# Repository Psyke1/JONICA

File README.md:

# JONICA

# ASIGNACION DE TAREAS

· JONI
- Diseño de actuadores para escape de tapas
- Control de motores paso a paso

· PAULA
- //Control de servo
- Comunicacion UART Arduino

· MARIANO
- Comunicacion UART en Python + definición de tramas
- Ver imagen por navegador (opcional)
- Puente H

· OPAMP
- Diseño de maqueta
- Algoritmo de reconocimiento
- Diseño de tolva

· TAREAS PENDIENTES
- Alimentacion a usar
- Motor de tolva (lo dejamos directo?)
- LEDs blancos (los dejamos directos?)
- Definir tramas de comunicación UART
- Probar la tolva

- Colores de tapas:
- Rojo, verde, celeste, amarillo, naranja, gris.

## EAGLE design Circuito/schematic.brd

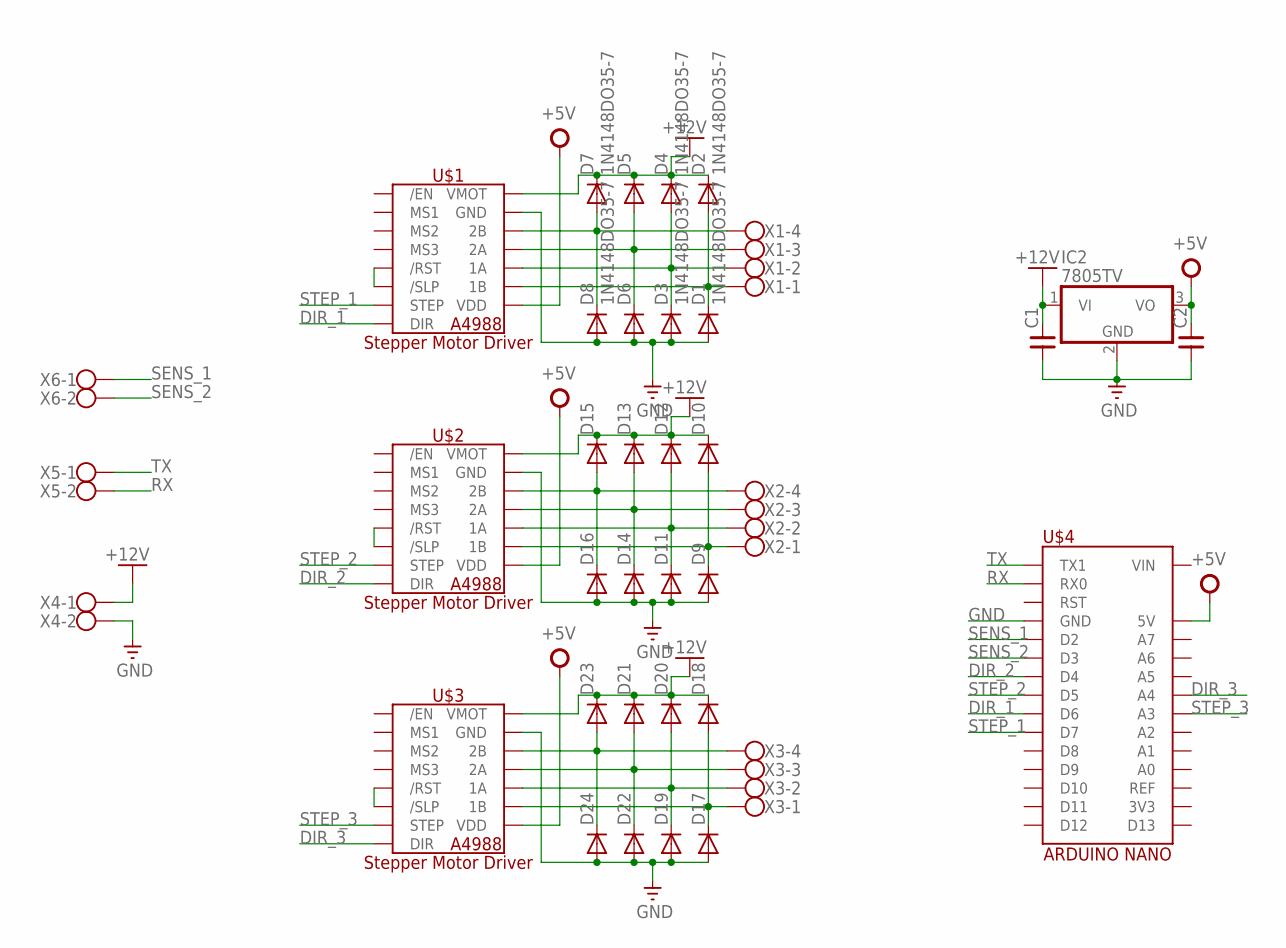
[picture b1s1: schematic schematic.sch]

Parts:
C1, C2: CNP-C035-055X025; C035-055X025
D1, D2, D3, D4, D5, D6, D7, D8, D9, D10, D11, D12, D13, D14, D15, D16, D17, D18, D19, D20, D21, D22, D23, D24: 1N4148DO35-7; DO35-7
IC2: 7805TV; TO220V
U$1, U$2, U$3: A4988_STEP
U$4: NANO_HEADER
X1, X2, X3: W237-4
X4, X5, X6: W237-102

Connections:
+5V: C2.2, IC2.3 (VO), U$1.VDD, U$2.VDD, U$3.VDD, U$4.5V
+12V: C1.2, D2.C, D4.C, D5.C, D7.C, D10.C, D12.C, D13.C, D15.C, D18.C, D20.C, D21.C, D23.C, IC2.1 (VI), U$1.VMOT, U$2.VMOT, U$3.VMOT, X4.1
DIR_1: U$1.DIR, U$4.D6
DIR_2: U$2.DIR, U$4.D4
DIR_3: U$3.DIR, U$4.A4
GND: C1.1, C2.1, D1.A, D3.A, D6.A, D8.A, D9.A, D11.A, D14.A, D16.A, D17.A, D19.A, D22.A, D24.A, IC2.2 (GND), U$1.GND, U$1.GND2 (GND), U$2.GND, U$2.GND2 (GND), U$3.GND, U$3.GND2 (GND), U$4.GND, U$4.GND2 (GND), X4.2
unnamed: D1.C, D2.A, U$1.1B, X1.1
unnamed: U$1./RST, U$1./SLP
unnamed: D9.C, D10.A, U$2.1B, X2.1
unnamed: D3.C, D4.A, U$1.1A, X1.2
unnamed: D11.C, D12.A, U$2.1A, X2.2
unnamed: D5.A, D6.C, U$1.2A, X1.3
unnamed: D7.A, D8.C, U$1.2B, X1.4
unnamed: D13.A, D14.C, U$2.2A, X2.3
unnamed: D15.A, D16.C, U$2.2B, X2.4
unnamed: U$2./RST, U$2./SLP
unnamed: D17.C, D18.A, U$3.1B, X3.1
unnamed: D19.C, D20.A, U$3.1A, X3.2
unnamed: D21.A, D22.C, U$3.2A, X3.3
unnamed: D23.A, D24.C, U$3.2B, X3.4
unnamed: U$3./RST, U$3./SLP
RX: U$4.RX0, X5.2
SENS_1: U$4.D2, X6.1
SENS_2: U$4.D3, X6.2
STEP_1: U$1.STEP, U$4.D7
STEP_2: U$2.STEP, U$4.D5
STEP_3: U$3.STEP, U$4.A3
TX: U$4.TX1, X5.1

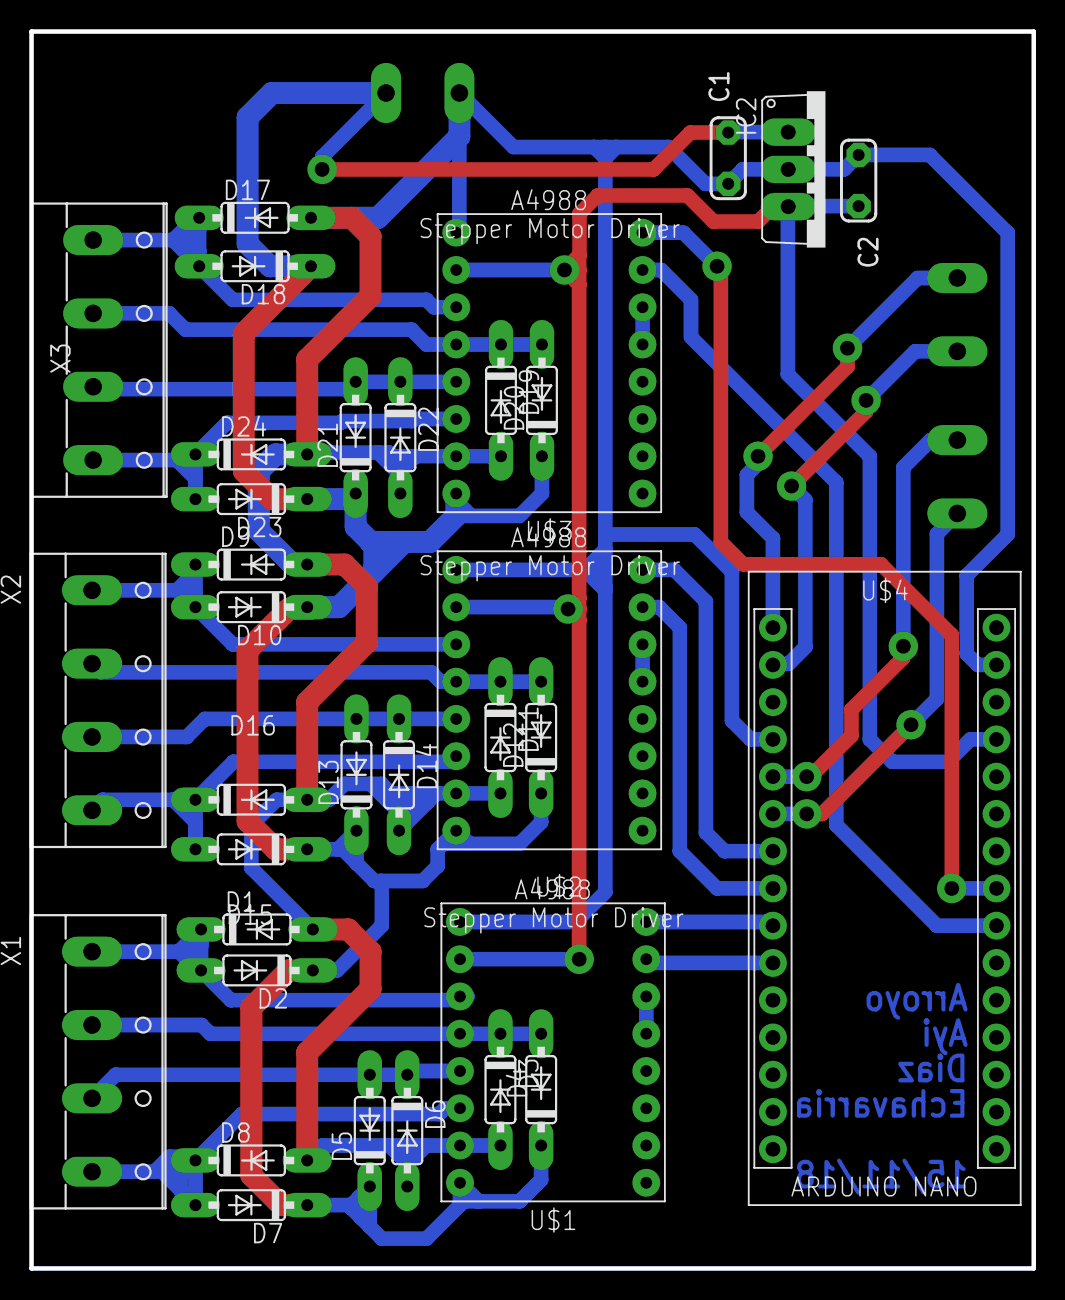
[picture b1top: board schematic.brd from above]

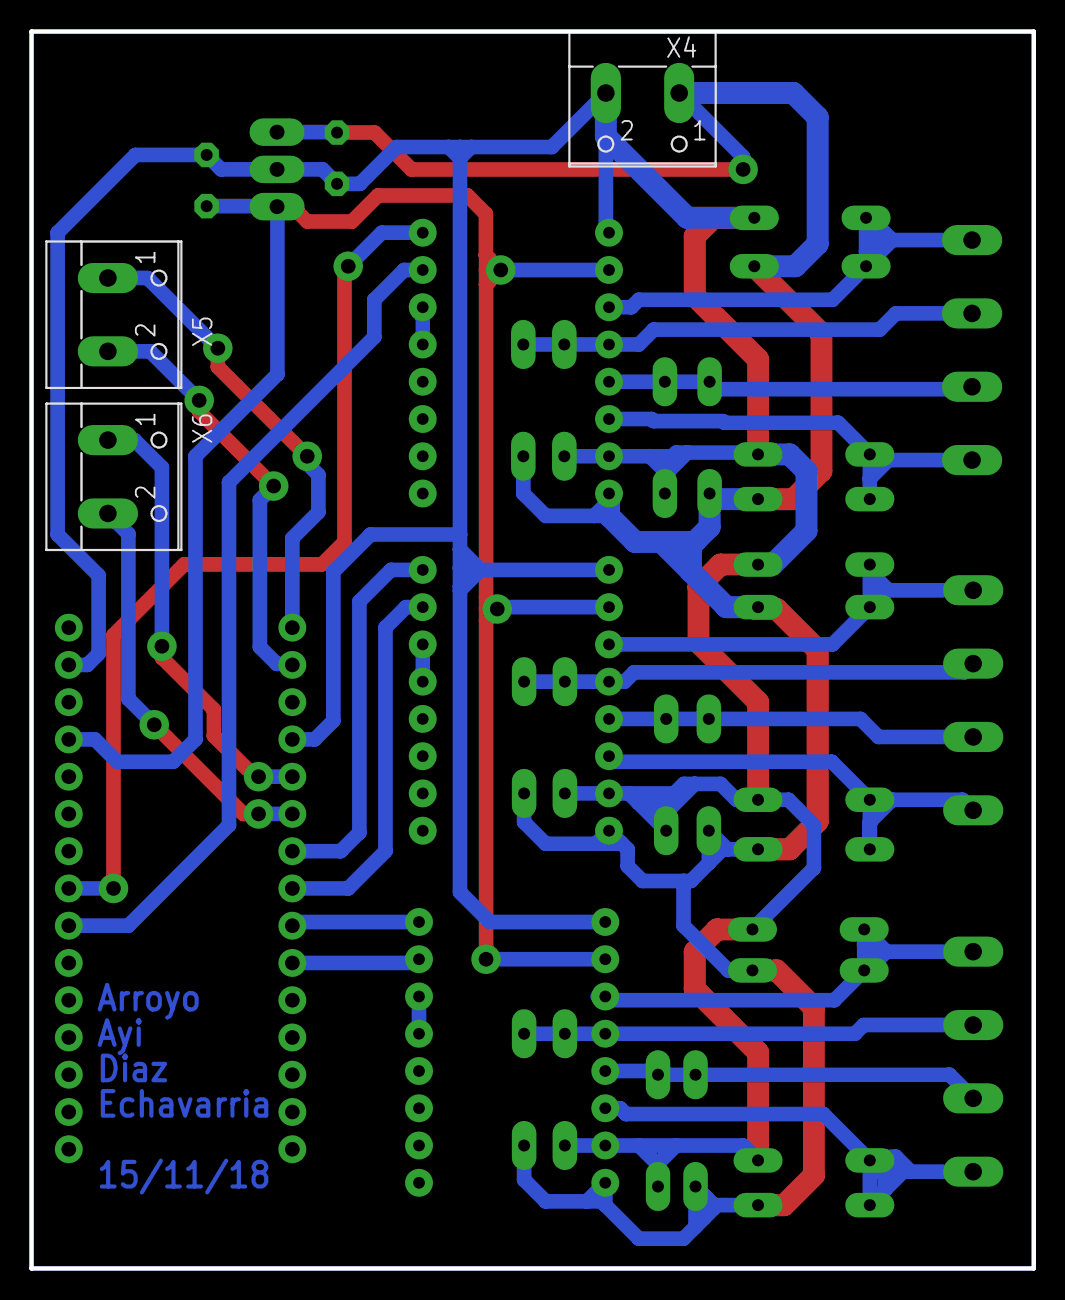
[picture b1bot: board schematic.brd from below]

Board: 2 copper layers, 68.3 x 84.3 mm, 37 parts (3 on the bottom side), 28 nets.

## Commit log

2018-08-31 Agregado color_sel_video.py
2018-08-31 Agregado el directorio Imagenes utiles

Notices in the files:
parts and their libraries:
supply0: Copyright (C) 2007, Bob Starr
